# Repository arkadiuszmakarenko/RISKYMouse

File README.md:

# RISKYMouse
RISKYMouse - Amiga DB9 - USB Hid Mouse Adapter

## Acknowledgments
Project is based on following projects:

 * Mist (USB HID parser stack)
 * Mouse Driver - sq7bti.
 * Simon Inns smallymouse2 mouse quadrature encoding

## PCB Project
This project does't provide PCB design, only schematics. You are free to design your own based on schematics provided.
You can use RISKYKVM as PCB design as those two projects are pin compatible.

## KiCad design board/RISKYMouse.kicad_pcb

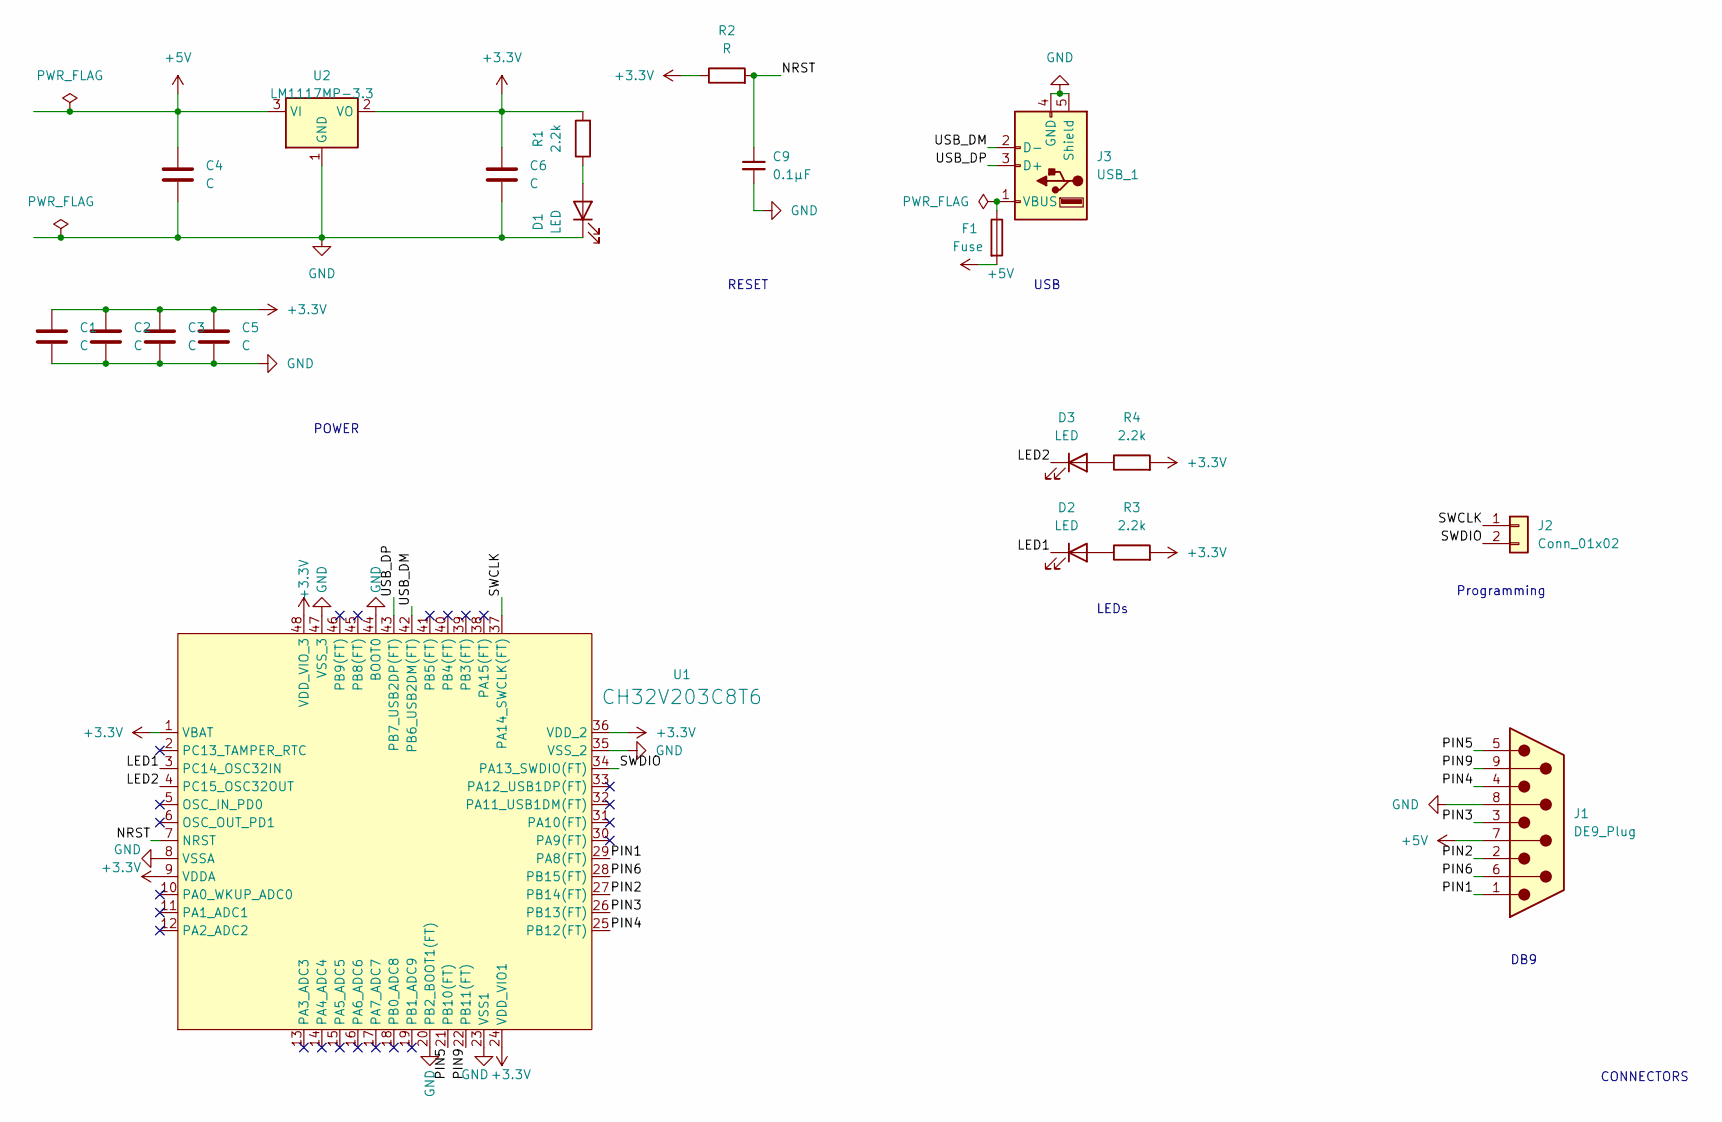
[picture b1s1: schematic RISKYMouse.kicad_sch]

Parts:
C1, C2, C3, C4, C5, C6: C; C_0603_1608Metric_Pad1.08x0.95mm_HandSolder
C9: 0.1μF; C_0603_1608Metric_Pad1.08x0.95mm_HandSolder; LCSC C14663
D1, D2, D3: LED; LED_0805_2012Metric_Pad1.15x1.40mm_HandSolder
F1: Fuse; Fuse_1206_3216Metric_Pad1.42x1.75mm_HandSolder
J1: DE9_Plug; DSUB-9_Female_EdgeMount_P2.77mm
J2: Conn_01x02; PinHeader_1x02_P2.54mm_Vertical
J3: USB_1; USB_A_CONNFLY_DS1095-WNR0
R1, R3, R4: 2.2k; R_0603_1608Metric_Pad0.98x0.95mm_HandSolder
R2: R; R_0603_1608Metric_Pad0.98x0.95mm_HandSolder
U1: CH32V203C8T6; LQFP-48_7x7mm_P0.5mm
U2: LM1117MP-3.3; SOT-89-3

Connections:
+3.3V: C1.1, C2.1, C3.1, C5.1, C6.1, R1.2, R2.1, R3.2, R4.2, U1.1 (VBAT), U1.9 (VDDA), U1.24 (VDD_VIO1), U1.36 (VDD_2), U1.48 (VDD_VIO_3), U2.2 (VO)
+5V: C4.1, F1.2, J1.7, U2.3 (VI)
/LED1: D2.1 (K), U1.3 (PC14_OSC32IN)
/LED2: D3.1 (K), U1.4 (PC15_OSC32OUT)
/NRST: C9.1, R2.2, U1.7 (NRST)
/PIN1: J1.1, U1.29 (PA8(FT))
/PIN2: J1.2, U1.27 (PB14(FT))
/PIN3: J1.3, U1.26 (PB13(FT))
/PIN4: J1.4, U1.25 (PB12(FT))
/PIN5: J1.5, U1.21 (PB10(FT))
/PIN6: J1.6, U1.28 (PB15(FT))
/PIN9: J1.9, U1.22 (PB11(FT))
/SWCLK: J2.1, U1.37 (PA14_SWCLK(FT))
/SWDIO: J2.2, U1.34 (PA13_SWDIO(FT))
/USB_DM: J3.2 (D-), U1.42 (PB6_USB2DM(FT))
/USB_DP: J3.3 (D+), U1.43 (PB7_USB2DP(FT))
GND: C1.2, C2.2, C3.2, C4.2, C5.2, C6.2, C9.2, D1.1 (K), J1.8, J3.4 (GND), J3.5 (Shield), U1.8 (VSSA), U1.20 (PB2_BOOT1(FT)), U1.23 (VSS1), U1.35 (VSS_2), U1.44 (BOOT0), U1.47 (VSS_3), U2.1 (GND)
unnamed: D1.2 (A), R1.1
unnamed: D2.2 (A), R3.1
unnamed: D3.2 (A), R4.1
unnamed: F1.1, J3.1 (VBUS)

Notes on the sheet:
USB
LEDs
Programming
POWER
CONNECTORS
DB9
RESET

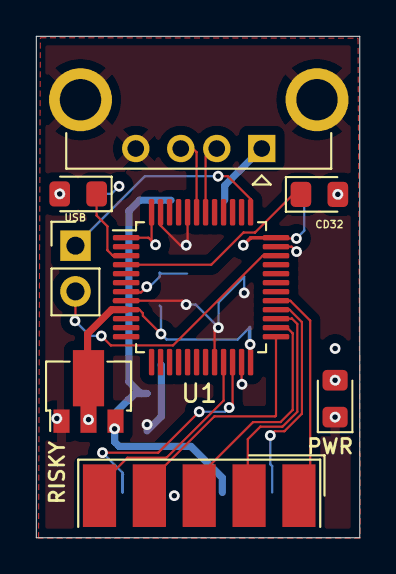
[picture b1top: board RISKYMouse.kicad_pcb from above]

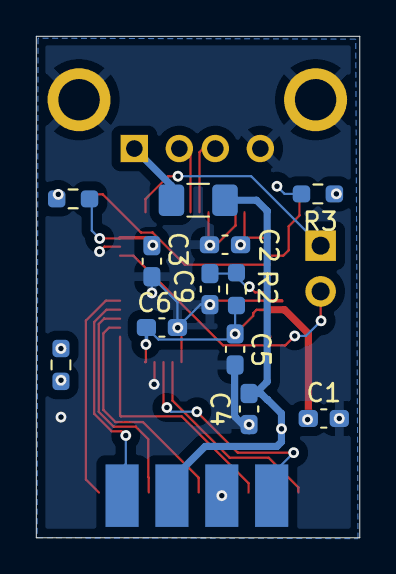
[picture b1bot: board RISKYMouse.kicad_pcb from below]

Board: 4 copper layers, 18.0 x 27.9 mm, 20 parts (12 on the bottom side), 21 nets.

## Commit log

2025-02-15 Release v0.1
2025-02-15 README update
2025-02-16 v0.2 Filename fixes
2026-01-12 New PCB design
2026-01-15 revised PCB
2026-01-17 proof of concept
2026-01-18 USB mappings fixed
2026-01-19 USB Gamepad detection, fixed mappings
2026-01-19 structure in place
2026-05-16 XBOX360 gampepads support
